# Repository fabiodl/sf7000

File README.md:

# sf7000

Most of the work was done by Andrea Ottaviani
https://github.com/aotta

If you find any error please let me know

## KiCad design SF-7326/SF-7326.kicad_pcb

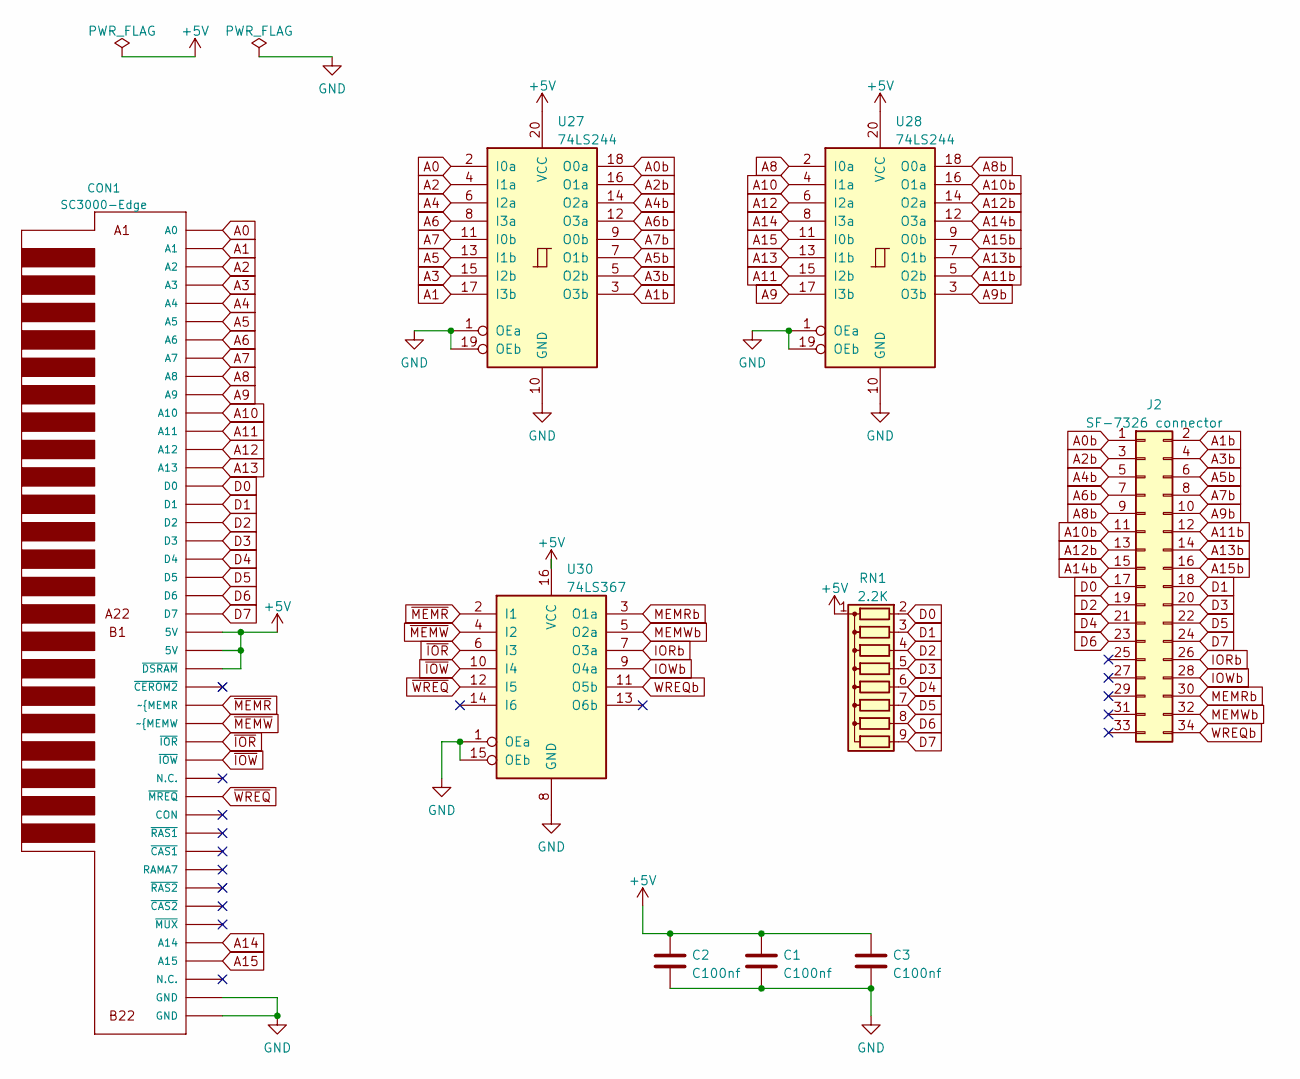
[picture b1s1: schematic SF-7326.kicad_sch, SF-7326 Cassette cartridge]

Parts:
C1, C2, C3: C100nf; C_Disc_D4.7mm_W2.5mm_P5.00mm
CON1: SC3000-Edge; SC3000_EDGE
J2: SF-7326 connector; IDC-Header_2x17_P2.54mm_Latch_Horizontal
RN1: 2.2K; R_Array_SIP9
U27, U28: 74LS244; DIP-20_W7.62mm_Socket
U30: 74LS367; DIP-16_W7.62mm_Socket

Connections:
+5V: C1.1, C2.1, C3.1, CON1.B1 (5V), CON1.B2 (5V), CON1.B3 (~DSRAM), RN1.1 (common), U27.20 (VCC), U28.20 (VCC), U30.16 (VCC)
A0: CON1.A1 (A0), U27.2 (I0a)
A0b: J2.1, U27.18 (O0a)
A1: CON1.A2 (A1), U27.17 (I3b)
A1b: J2.2, U27.3 (O3b)
A2: CON1.A3 (A2), U27.4 (I1a)
A2b: J2.3, U27.16 (O1a)
A3: CON1.A4 (A3), U27.15 (I2b)
A3b: J2.4, U27.5 (O2b)
A4: CON1.A5 (A4), U27.6 (I2a)
A4b: J2.5, U27.14 (O2a)
A5: CON1.A6 (A5), U27.13 (I1b)
A5b: J2.6, U27.7 (O1b)
A6: CON1.A7 (A6), U27.8 (I3a)
A6b: J2.7, U27.12 (O3a)
A7: CON1.A8 (A7), U27.11 (I0b)
A7b: J2.8, U27.9 (O0b)
A8: CON1.A9 (A8), U28.2 (I0a)
A8b: J2.9, U28.18 (O0a)
A9: CON1.A10 (A9), U28.17 (I3b)
A9b: J2.10, U28.3 (O3b)
A10: CON1.A11 (A10), U28.4 (I1a)
A10b: J2.11, U28.16 (O1a)
A11: CON1.A12 (A11), U28.15 (I2b)
A11b: J2.12, U28.5 (O2b)
A12: CON1.A13 (A12), U28.6 (I2a)
A12b: J2.13, U28.14 (O2a)
A13: CON1.A14 (A13), U28.13 (I1b)
A13b: J2.14, U28.7 (O1b)
A14: CON1.B18 (A14), U28.8 (I3a)
A14b: J2.15, U28.12 (O3a)
A15: CON1.B19 (A15), U28.11 (I0b)
A15b: J2.16, U28.9 (O0b)
D0: CON1.A15 (D0), J2.17, RN1.2 (R1)
D1: CON1.A16 (D1), J2.18, RN1.3 (R2)
D2: CON1.A17 (D2), J2.19, RN1.4 (R3)
D3: CON1.A18 (D3), J2.20, RN1.5 (R4)
D4: CON1.A19 (D4), J2.21, RN1.6 (R5)
D5: CON1.A20 (D5), J2.22, RN1.7 (R6)
D6: CON1.A21 (D6), J2.23, RN1.8 (R7)
D7: CON1.A22 (D7), J2.24, RN1.9 (R8)
GND: C1.2, C2.2, C3.2, CON1.B21 (GND), CON1.B22 (GND), U27.1 (OEa), U27.10 (GND), U27.19 (OEb), U28.1 (OEa), U28.10 (GND), U28.19 (OEb), U30.1 (OEa), U30.8 (GND), U30.15 (OEb)
IORb: J2.26, U30.7 (O3a)
IOWb: J2.28, U30.9 (O4a)
MEMRb: J2.30, U30.3 (O1a)
MEMWb: J2.32, U30.5 (O2a)
WREQb: J2.34, U30.11 (O5b)
~IOR: CON1.B7 (~IOR), U30.6 (I3)
~IOW: CON1.B8 (~IOW), U30.10 (I4)
~MEMR: CON1.B5 (~{MEMR), U30.2 (I1)
~MEMW: CON1.B6 (~{MEMW), U30.4 (I2)
~WREQ: CON1.B10 (~MREQ), U30.12 (I5)

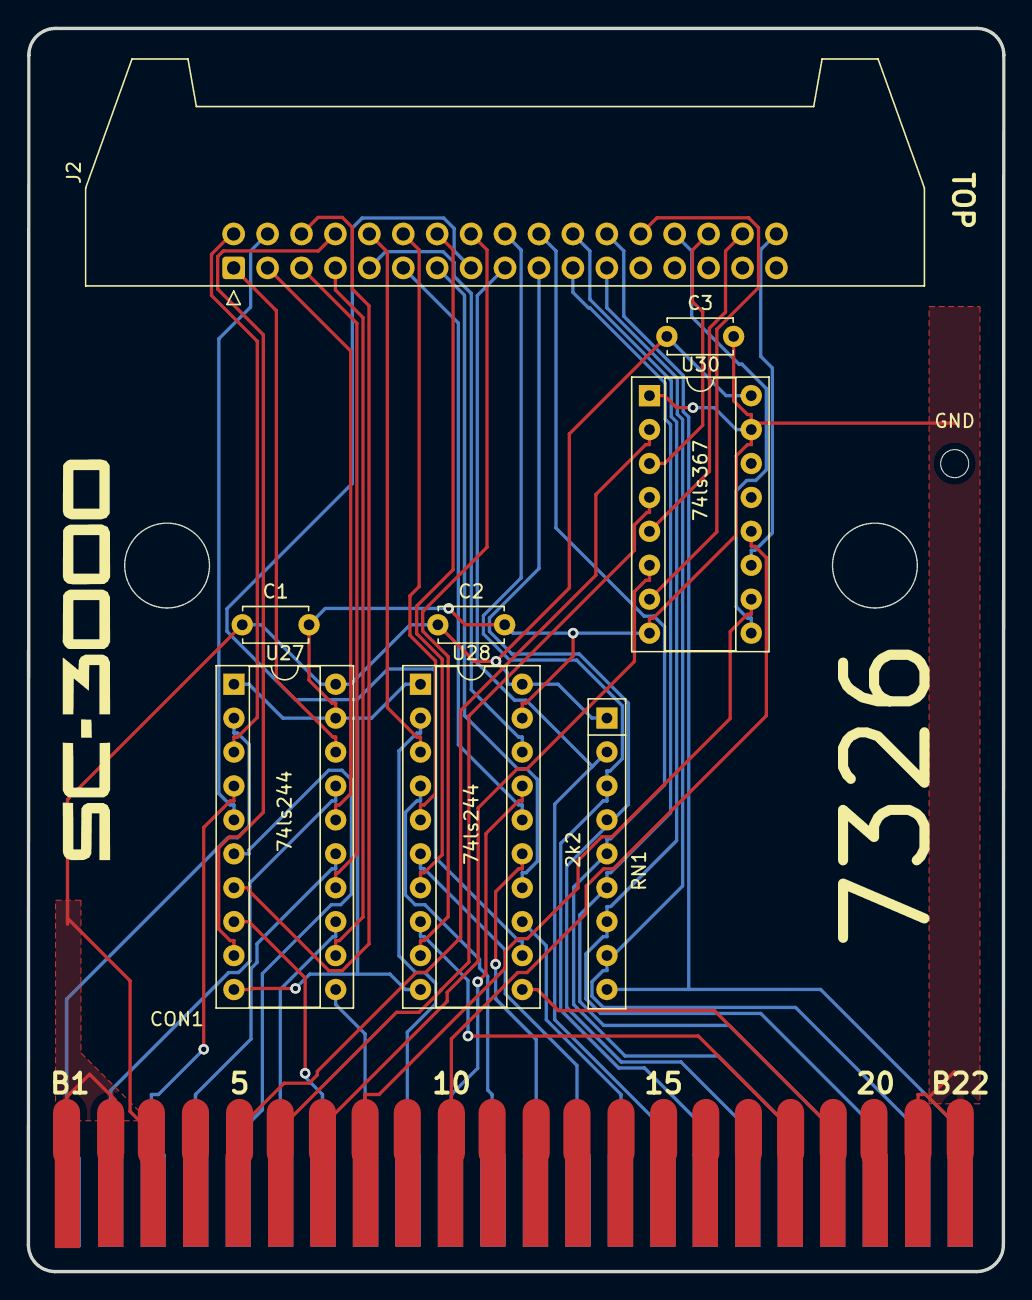
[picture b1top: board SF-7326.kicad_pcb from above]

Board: 2 copper layers, 73.0 x 93.1 mm, 10 parts (0 on the bottom side), 52 nets.

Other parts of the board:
GND: MountingHole_2.1mm

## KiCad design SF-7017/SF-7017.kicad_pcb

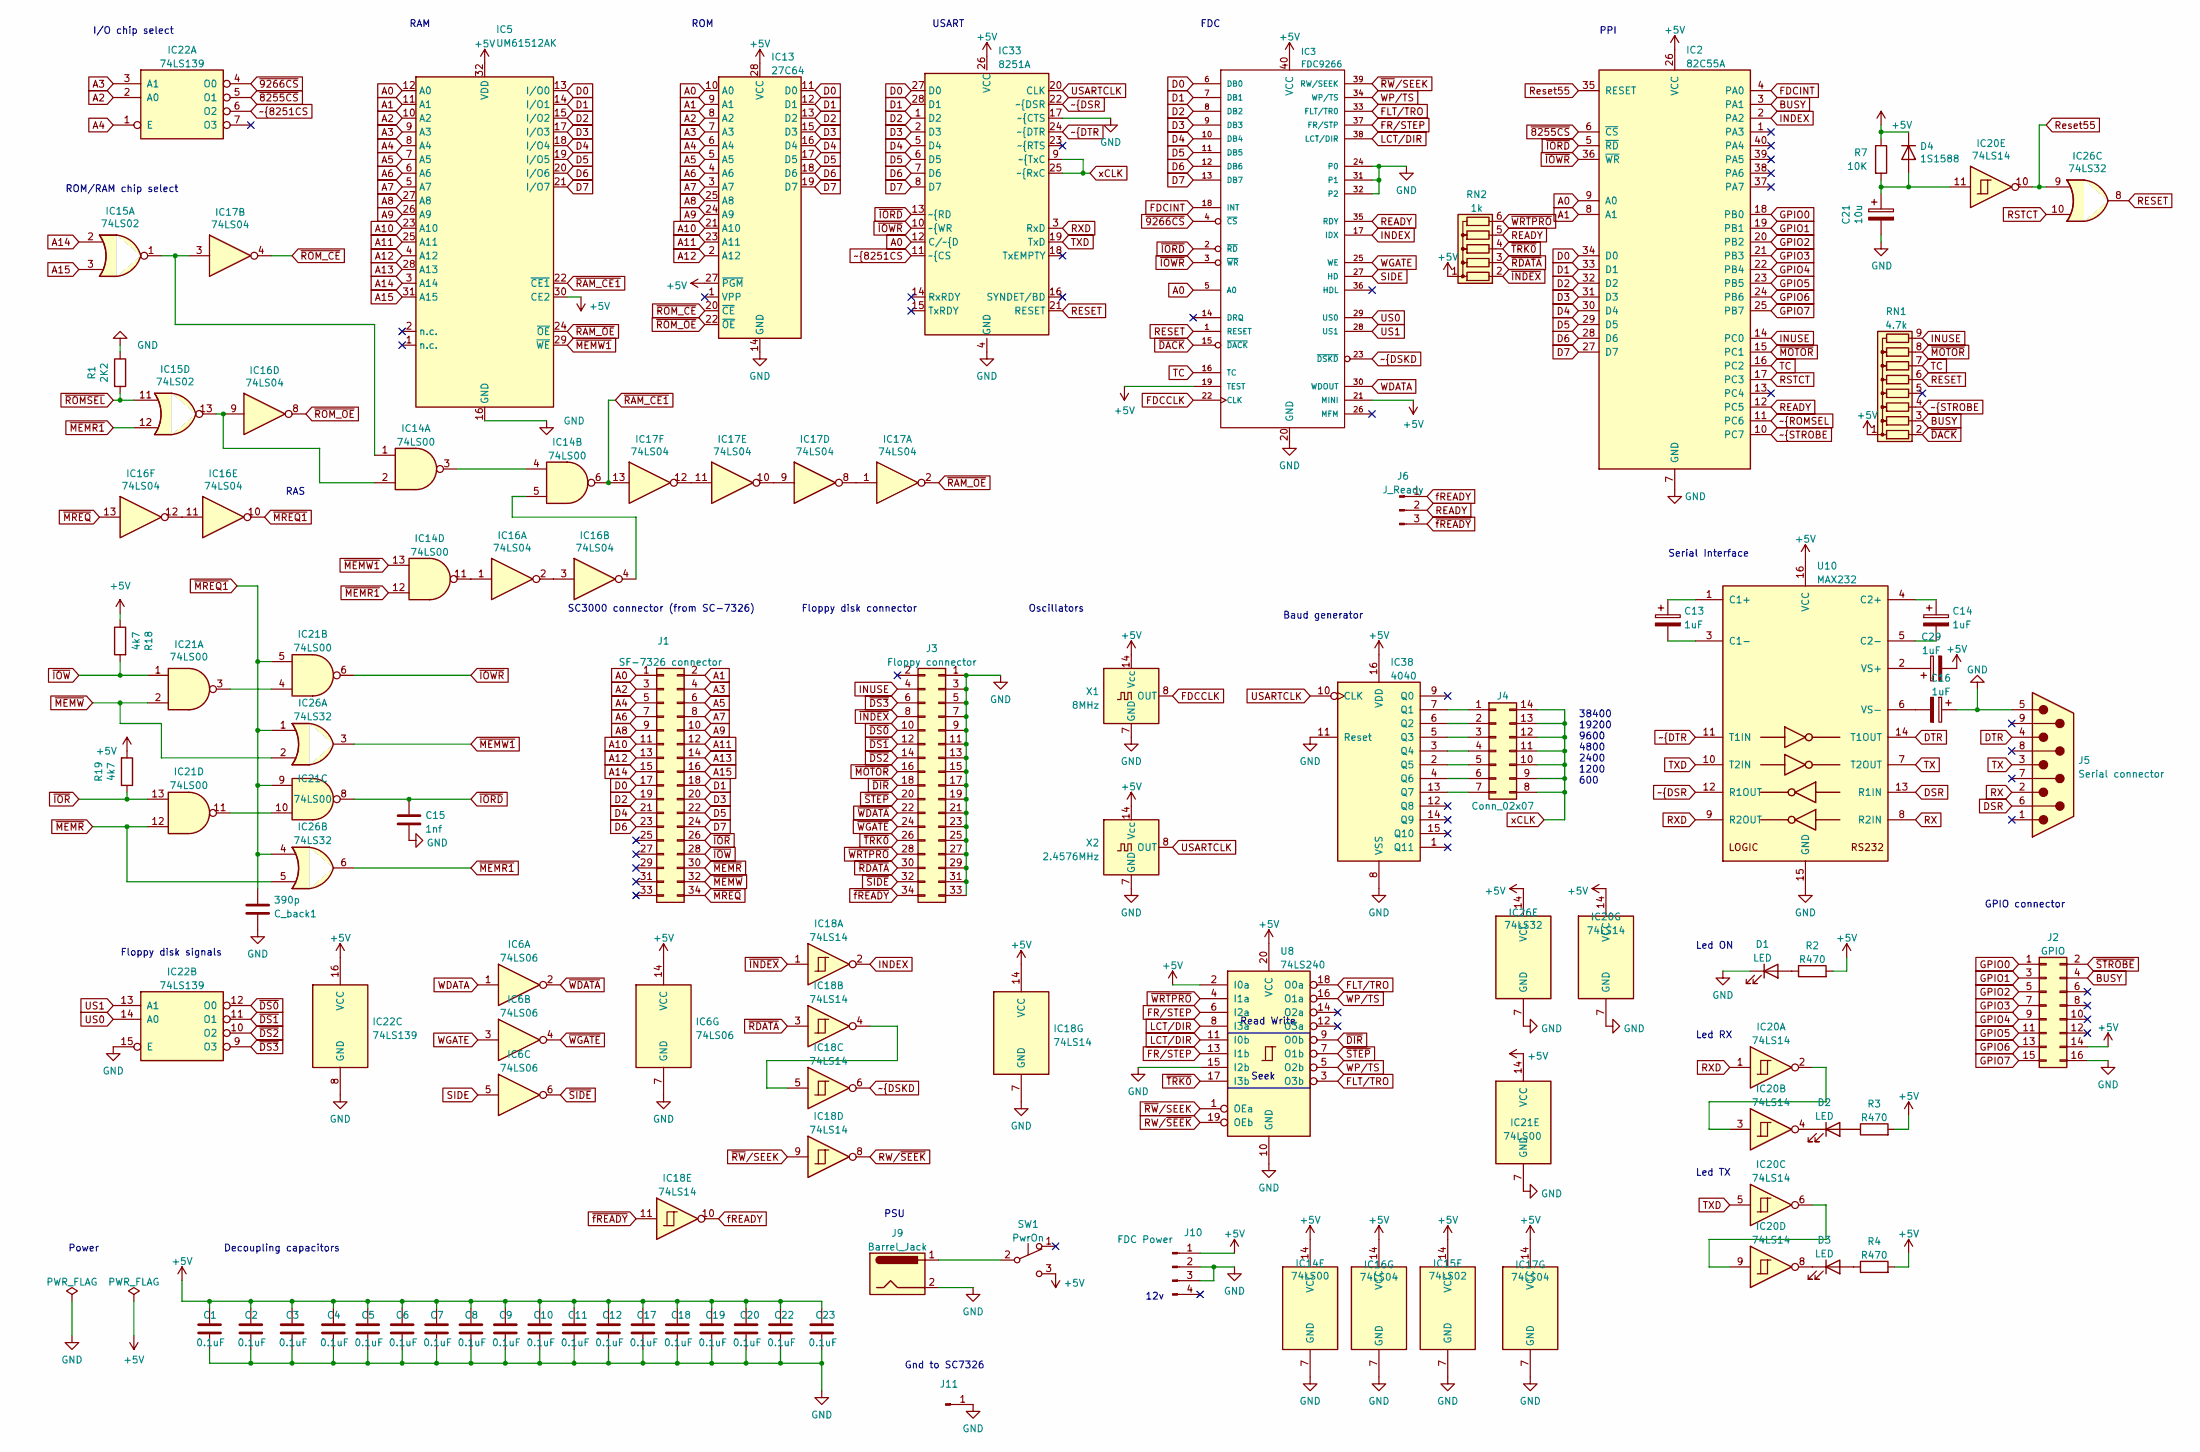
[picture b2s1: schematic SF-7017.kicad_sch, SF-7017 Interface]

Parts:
C1, C2, C3, C4, C5, C6, C7, C8, C9, C10, C11, C12, C17, C18, C19, C20, C22, C23: 0.1uF; C_Disc_D4.7mm_W2.5mm_P5.00mm
C13, C14, C16, C29: 1uF; CP_Radial_D5.0mm_P2.00mm
C15: 1nf; C_Disc_D5.0mm_W2.5mm_P5.00mm
C21: 10u; CP_Radial_D5.0mm_P2.50mm
C_back1: 390p
D1, D2, D3: LED; LED_Rectangular_W3.0mm_H2.0mm
D4: 1S1588; D_DO-34_SOD68_P7.62mm_Horizontal
IC2: 82C55A; DIP-40_W15.24mm
IC3: FDC9266; DIP-40_W15.24mm_Socket
IC5: UM61512AK; DIP-32_W7.62mm
IC6: 74LS06; DIP-14_W7.62mm_Socket
IC13: 27C64; DIP-28_W15.24mm
IC14, IC21: 74LS00; DIP-14_W7.62mm
IC15: 74LS02; DIP-14_W7.62mm_Socket
IC16, IC17: 74LS04; DIP-14_W7.62mm
IC18, IC20: 74LS14; DIP-14_W7.62mm_Socket
IC22: 74LS139; DIP-16_W7.62mm_Socket
IC26: 74LS32; DIP-14_W7.62mm_Socket
IC33: 8251A; DIP-28_W15.24mm_Socket
IC38: 4040; DIP-16_W7.62mm
J1: SF-7326 connector; IDC-Header_2x17_P2.54mm_Horizontal
J2: GPIO; PinHeader_2x08_P2.54mm_Vertical
J3: Floppy connector; IDC-Header_2x17_P2.54mm_Horizontal
J4: Conn_02x07; SW_DIP_SPSTx07_Slide_6.7x19.34mm_W7.62mm_P2.54mm_LowProfile
J5: Serial connector; DSUB-9_Male_Horizontal_P2.77x2.84mm_EdgePinOffset4.94mm_Hou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
J6: J_Ready; PinHeader_1x03_P2.54mm_Vertical
J9: Barrel_Jack; BarrelJack_Horizontal
J10: FDC Power; Molex_SL_171971-0004_1x04_P2.54mm_Vertical
J11: GND; PinHeader_1x01_P2.54mm_Horizontal
R1: 2K2; R_Axial_DIN0204_L3.6mm_D1.6mm_P7.62mm_Horizontal
R2, R3, R4: R470; R_Axial_DIN0204_L3.6mm_D1.6mm_P7.62mm_Horizontal
R7: 10K; R_Axial_DIN0204_L3.6mm_D1.6mm_P7.62mm_Horizontal
R18, R19: 4k7; R_Axial_DIN0204_L3.6mm_D1.6mm_P7.62mm_Horizontal
RN1: 4.7k; R_Array_SIP9
RN2: 1k; R_Array_SIP6
SW1: PwrOn; Rocker Switch_TE_1-1571986-1
U8: 74LS240; DIP-20_W7.62mm_Socket
U10: MAX232; DIP-16_W7.62mm
X1: 8MHz; Oscillator_DIP-14
X2: 2.4576MHz; Oscillator_DIP-14

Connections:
+5V: C1.1, C2.1, C3.1, C4.1, C5.1, C6.1, C7.1, C8.1, C9.1, C10.1, C11.1, C12.1, C17.1, C18.1, C19.1, C20.1, C22.1, C23.1, C29.2, D4.1 (K), IC2.26 (VCC), IC3.19 (TEST), IC3.21 (MINI), IC3.40 (VCC), IC5.30 (CE2), IC5.32 (VDD), IC6.14 (VCC), IC13.27 (~PGM), IC13.28 (VCC), IC14.14 (VCC), IC15.14 (VCC), IC16.14 (VCC), IC17.14 (VCC), IC18.14 (VCC), IC20.14 (VCC), IC21.14 (VCC), IC22.16 (VCC), IC26.14 (VCC), IC33.26 (VCC), IC38.16 (VDD), J2.14, J10.1, R2.2, R3.2, R4.2, R7.1, R18.1, R19.2, RN1.1 (common), RN2.1 (common), SW1.3 (C), U8.2 (I0a), U8.20 (VCC), U10.16 (VCC), X1.14 (Vcc), X2.14 (Vcc)
A0: IC2.9 (A0), IC3.5 (A0), IC5.12 (A0), IC13.10 (A0), IC33.12 (C/~{D), J1.1
A1: IC2.8 (A1), IC5.11 (A1), IC13.9 (A1), J1.2
A2: IC5.10 (A2), IC13.8 (A2), IC22.2 (A0), J1.3
A3: IC5.9 (A3), IC13.7 (A3), IC22.3 (A1), J1.4
A4: IC5.8 (A4), IC13.6 (A4), IC22.1 (E), J1.5
A5: IC5.7 (A5), IC13.5 (A5), J1.6
A6: IC5.6 (A6), IC13.4 (A6), J1.7
A7: IC5.5 (A7), IC13.3 (A7), J1.8
A8: IC5.27 (A8), IC13.25 (A8), J1.9
A9: IC5.26 (A9), IC13.24 (A9), J1.10
A10: IC5.23 (A10), IC13.21 (A10), J1.11
A11: IC5.25 (A11), IC13.23 (A11), J1.12
A12: IC5.4 (A12), IC13.2 (A12), J1.13
A13: IC5.28 (A13), J1.14
A14: IC5.3 (A14), IC15.2, J1.15
A15: IC5.31 (A15), IC15.3, J1.16
BUSY: IC2.3 (PA1), J2.4, RN1.3 (R2)
D0: IC2.34 (D0), IC3.6 (DB0), IC5.13 (I/O0), IC13.11 (D0), IC33.27 (D0), J1.17
D1: IC2.33 (D1), IC3.7 (DB1), IC5.14 (I/O1), IC13.12 (D1), IC33.28 (D1), J1.18
D2: IC2.32 (D2), IC3.8 (DB2), IC5.15 (I/O2), IC13.13 (D2), IC33.1 (D2), J1.19
D3: IC2.31 (D3), IC3.9 (DB3), IC5.17 (I/O3), IC13.15 (D3), IC33.2 (D3), J1.20
D4: IC2.30 (D4), IC3.10 (DB4), IC5.18 (I/O4), IC13.16 (D4), IC33.5 (D4), J1.21
D5: IC2.29 (D5), IC3.11 (DB5), IC5.19 (I/O5), IC13.17 (D5), IC33.6 (D5), J1.22
D6: IC2.28 (D6), IC3.12 (DB6), IC5.20 (I/O6), IC13.18 (D6), IC33.7 (D6), J1.23
D7: IC2.27 (D7), IC3.13 (DB7), IC5.21 (I/O7), IC13.19 (D7), IC33.8 (D7), J1.24
DSR: J5.6, U10.13 (R1IN)
DTR: J5.4, U10.14 (T1OUT)
FDCCLK: IC3.22 (CLK), X1.8 (OUT)
FDCINT: IC2.4 (PA0), IC3.18 (INT)
FLT/TRO: IC3.33 (FLT/TR0), U8.3 (O3b), U8.18 (O0a)
FR/STEP: IC3.37 (FR/STP), U8.6 (I2a), U8.13 (I1b)
GND: C1.2, C2.2, C3.2, C4.2, C5.2, C6.2, C7.2, C8.2, C9.2, C10.2, C11.2, C12.2, C15.2, C16.1, C17.2, C18.2, C19.2, C20.2, C21.2, C22.2, C23.2, C_back1.1, D1.1 (K), IC2.7 (GND), IC3.20 (GND), IC3.24 (P0), IC3.31 (P1), IC3.32 (P2), IC5.16 (GND), IC6.7 (GND), IC13.14 (GND), IC14.7 (GND), IC15.7 (GND), IC16.7 (GND), IC17.7 (GND), IC18.7 (GND), IC20.7 (GND), IC21.7 (GND), IC22.8 (GND), IC22.15 (E), IC26.7 (GND), IC33.4 (GND), IC33.17 (~{CTS), IC38.8 (VSS), IC38.11 (Reset), J2.16, J3.1, J3.3, J3.5, J3.7, J3.9, J3.11, J3.13, J3.15, J3.17, J3.19, J3.21, J3.23, J3.25, J3.27, J3.29, J3.31, J3.33, J5.5, J9.2, J10.2, J10.3, J11.1, R1.1, U8.10 (GND), U8.15 (I2b), U10.15 (GND), X1.7 (GND), X2.7 (GND)
GPIO0: IC2.18 (PB0), J2.1
GPIO1: IC2.19 (PB1), J2.3
GPIO2: IC2.20 (PB2), J2.5
GPIO3: IC2.21 (PB3), J2.7
GPIO4: IC2.22 (PB4), J2.9
GPIO5: IC2.23 (PB5), J2.11
GPIO6: IC2.24 (PB6), J2.13
GPIO7: IC2.25 (PB7), J2.15
INDEX: IC2.2 (PA2), IC3.17 (IDX), IC18.2
INUSE: IC2.14 (PC0), J3.4, RN1.9 (R8)
LCT/DIR: IC3.38 (LCT/DIR), U8.8 (I3a), U8.11 (I0b)
unnamed: C13.1, U10.1 (C1+)
unnamed: C13.2, U10.3 (C1-)
unnamed: C14.1, U10.4 (C2+)
unnamed: C14.2, U10.5 (C2-)
unnamed: C16.2, U10.6 (VS-)
unnamed: C21.1, D4.2 (A), IC20.11, R7.2
unnamed: C29.1, U10.2 (VS+)
unnamed: D1.2 (A), R2.1
unnamed: D2.1 (K), IC20.4
unnamed: D2.2 (A), R3.1
unnamed: D3.1 (K), IC20.8
unnamed: D3.2 (A), R4.1
unnamed: IC14.1, IC15.1, IC17.3
unnamed: IC14.2, IC15.13, IC16.9
unnamed: IC14.3, IC14.4
unnamed: IC14.5, IC16.4
unnamed: IC14.11, IC16.1
unnamed: IC16.2, IC16.3
unnamed: IC16.11, IC16.12
unnamed: IC17.1, IC17.8
unnamed: IC17.9, IC17.10
unnamed: IC17.11, IC17.12
unnamed: IC18.4, IC18.5
unnamed: IC20.2, IC20.3
unnamed: IC20.6, IC20.9
unnamed: IC21.3, IC21.4
unnamed: IC21.10, IC21.11
unnamed: IC38.2 (Q5), J4.5
unnamed: IC38.3 (Q4), J4.4
unnamed: IC38.4 (Q6), J4.6
unnamed: IC38.5 (Q3), J4.3
unnamed: IC38.6 (Q2), J4.2
unnamed: IC38.7 (Q1), J4.1
unnamed: IC38.13 (Q7), J4.7
unnamed: J9.1, SW1.2 (B)
READY: IC2.12 (PC5), IC3.35 (RDY), J6.2, RN2.5 (R4)
RESET: IC3.1 (RESET), IC26.8, IC33.21 (RESET), RN1.6 (R5)
RSTCT: IC2.17 (PC3), IC26.10
RW/~SEEK: IC18.8, U8.19 (OEb)
RX: J5.2, U10.8 (R2IN)
RXD: IC20.1, IC33.3 (RxD), U10.9 (R2OUT)
Reset55: IC2.35 (RESET), IC20.10, IC26.9
SIDE: IC3.27 (HD), IC6.5
TC: IC2.16 (PC2), IC3.16 (TC), RN1.7 (R6)
TX: J5.3, U10.7 (T2OUT)
TXD: IC20.5, IC33.19 (TxD), U10.10 (T2IN)
US0: IC3.29 (US0), IC22.14 (A0)
US1: IC3.28 (US1), IC22.13 (A1)
USARTCLK: IC33.20 (CLK), IC38.10 (CLK), X2.8 (OUT)
WDATA: IC3.30 (WDOUT), IC6.1
WGATE: IC3.25 (WE), IC6.3
WP/TS: IC3.34 (WP/TS), U8.5 (O2b), U8.16 (O1a)
fREADY: IC18.10, J6.1
xCLK: IC33.9 (~{TxC), IC33.25 (~{RxC), J4.8, J4.9, J4.10, J4.11, J4.12, J4.13, J4.14
~8251CS: IC22.6 (O2), IC33.11 (~{CS)
~8255CS: IC2.6 (~CS), IC22.5 (O1)
~9266CS: IC3.4 (~CS), IC22.4 (O0)
~DACK: IC3.15 (~DACK), RN1.2 (R1)
~DIR: J3.18, U8.9 (O0b)
~DS0: IC22.12 (O0), J3.10
~DS1: IC22.11 (O1), J3.12
~DS2: IC22.10 (O2), J3.14
~DS3: IC22.9 (O3), J3.6
~DSKD: IC3.23 (~DSKD), IC18.6
~DSR: IC33.22 (~{DSR), U10.12 (R1OUT)
~DTR: IC33.24 (~{DTR), U10.11 (T1IN)
~INDEX: IC18.1, J3.8, RN2.2 (R1)
~IORD: C15.1, IC2.5 (~RD), IC3.2 (~RD), IC21.8, IC33.13 (~{RD)
~IOR: IC21.13, J1.26, R19.1
~IOWR: IC2.36 (~WR), IC3.3 (~WR), IC21.6, IC33.10 (~{WR)
~IOW: IC21.1, J1.28, R18.2
~MEMR1: IC14.12, IC15.12, IC26.6
~MEMR: IC21.12, IC26.5, J1.30
~MEMW1: IC5.29 (~WE), IC14.13, IC26.3
~MEMW: IC21.2, IC26.2, J1.32
~MOTOR: IC2.15 (PC1), J3.16, RN1.8 (R7)
~MREQ1: C_back1.2, IC16.10, IC21.5, IC21.9, IC26.1, IC26.4
~MREQ: IC16.13, J1.34
~RAM_CE1: IC5.22 (~CE1), IC14.6, IC17.13
~RAM_OE: IC5.24 (~OE), IC17.2
~RDATA: IC18.3, J3.30, RN2.3 (R2)
~ROM_CE: IC13.20 (~CE), IC17.4
~ROM_OE: IC13.22 (~OE), IC16.8
~RW/SEEK: IC3.39 (RW/SEEK), IC18.9, U8.1 (OEa)
~SIDE: IC6.6, J3.32
~STEP: J3.20, U8.7 (O1b)
~TRK0: J3.26, RN2.4 (R3), U8.17 (I3b)
~WDATA: IC6.2, J3.22
~WGATE: IC6.4, J3.24
~WRTPRO: J3.28, RN2.6 (R5), U8.4 (I1a)
~fREADY: IC18.11, J3.34, J6.3

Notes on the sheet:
Floppy disk connector
Decoupling capacitors
Gnd to SC7326
Led ON
I/O chip select
SC3000 connector (from SC-7326)
Power
Led TX
RAS
Oscillators
PPI
Floppy disk signals
RAM
Led RX
38400 19200 9600 4800 2400 1200 600
12v
GPIO connector
ROM/RAM chip select
Read Write
PSU
FDC
Serial Interface
Baud generator
USART
Seek
ROM

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
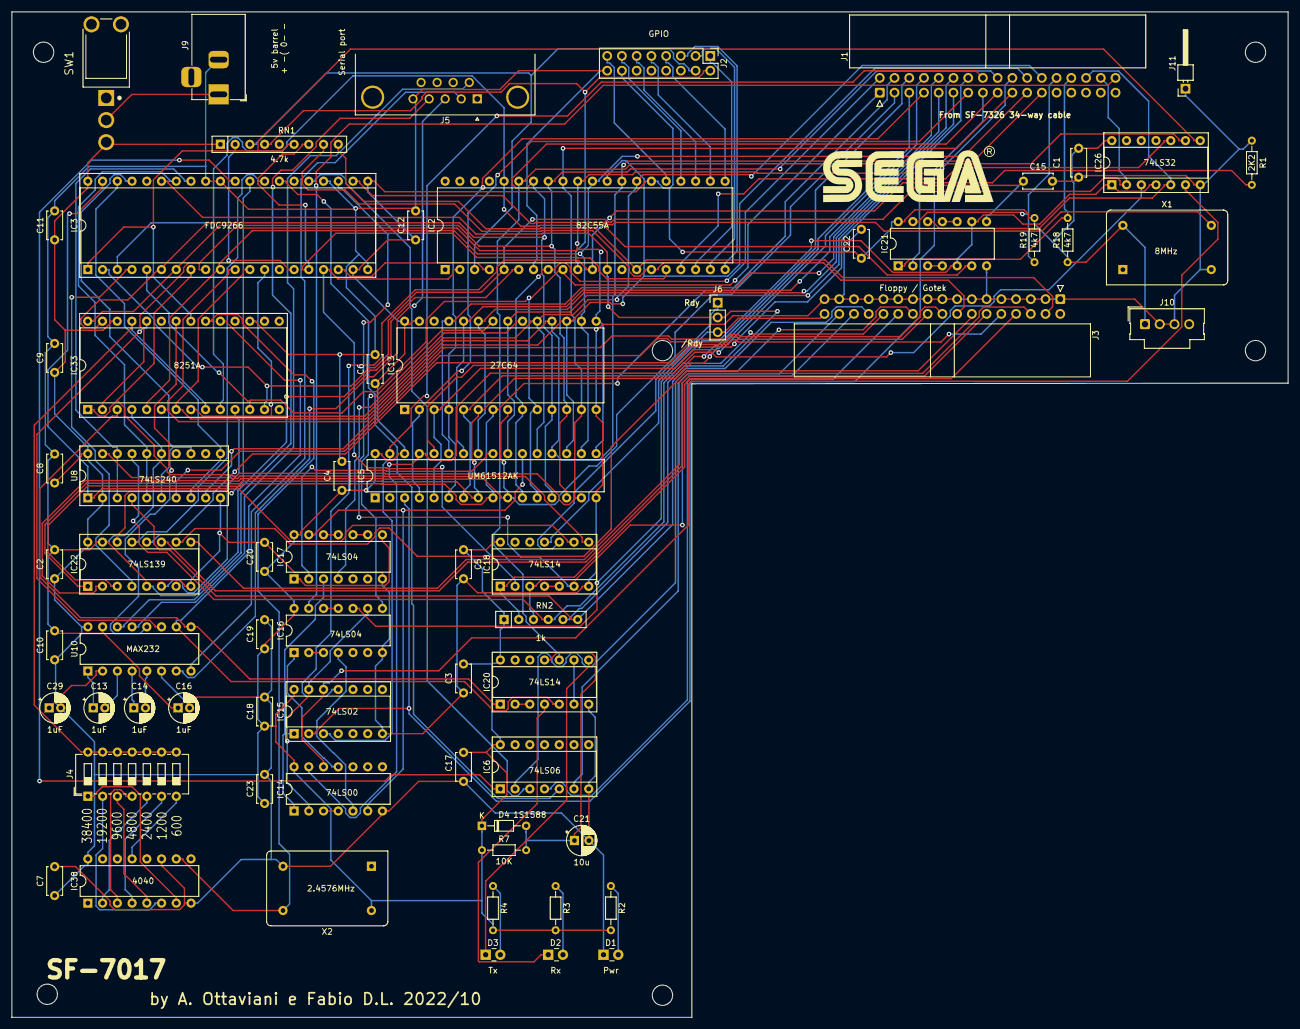
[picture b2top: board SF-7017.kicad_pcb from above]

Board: 2 copper layers, 220.0 x 173.3 mm, 67 parts (0 on the bottom side), 137 nets.

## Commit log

2022-08-19 moved to kicad 6
2022-08-19 labeled IC33
2022-08-19 IC25, info from andrea applied
2022-08-19 symbol for polarized cap
2022-08-23 traced address decoding logic
2022-10-30 Add files via upload
    I/O Cassette cart
2022-10-31 Added SF7017 and SC7326 projects (#1)
    * Add files via upload
    * Add files via upload
    I/O Cassette cart
    * Delete SC3000_logo.kicad_mod
    * Delete SF-7017/SC3000.pretty directory
